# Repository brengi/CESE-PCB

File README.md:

# DCI- Curso de Diseño de Circuitos Impresos de la Carrera de Especialización en Sistemas Embebidos #

El Curso de Diseño de Circuitos Impresos (DCI) es una asignatura optativa de la Carrera de Especialización en Sistemas Embebidos (CESE) de la Facultad de Ingeniería de la Universidad de Buenos Aires (FIUBA). Tiene una duración de dos meses, organizados en 8 clases semanales de 3 hs cada una. Para aprobar la asignatura los participantes deben realizar el diseño de un circuito impreso a elección durante el curso. En esta página quedan registradas  dichas prácticas.

Más info sobre el curso en las siguiente páginas: 
  * [Contenido y Bibliografía](https://sites.google.com/site/disenodecircuitosimpresoscese/home)
  * [Campus FIUBA](https://campus.fi.uba.ar/enrol/index.php?id=1450])

**ADVERTENCIA**: Estos diseños se realizan en tiempos muy cortos y no todos reciben una revisión funcional detallada. 
El curso enfoca el los procedimientos de diseño de Esquemático y de PCB y no en el diseño funcional de los  circuitos.
El uso de estos circuitos queda bajo la propia responsabilidad del usuario. 

   * [CURSO 2020 B](README_2020B.md#curso-2020-b)
      * [Sistema Monitoreo Alarma de Incendio](README_2020B.md#sistema-monitoreo-alarma-de-incendio)
      * [Réplica dc motor control](README_2020B.md#réplica-dc-motor-control)
      * [Titulador automático](README_2020B.md#titulador-automático)
      * [Board_NFC (Replica sin antena)](README_2020B.md#board_nfc-replica-sin-antena)
      * [Poncho TCP/IP](README_2020B.md#poncho-tcpip)
      * [Replica ESP01 (Mejorada)](README_2020B.md#replica-esp01-mejorada)
      * [Driver motor PAP y ADC](README_2020B.md#driver-motor-pap-y-adc)
      * [Helctec LoRa con cambios](README_2020B.md#helctec-lora-con-cambios)
      * [Réplica pro micro sparkfun (similar)](README_2020B.md#réplica-pro-micro-sparkfun-similar)
      * [Conversor de niveles lógicos](README_2020B.md#conversor-de-niveles-lógicos)
      * [Réplica Sparkfun VS1063](README_2020B.md#réplica-sparkfun-vs1063)
      * [Módulo de velocidad tacométrico](README_2020B.md#módulo-de-velocidad-tacométrico)
      * [Réplica Arduino nano 340g 2016](README_2020B.md#réplica-arduino-nano-340g-2016)
      * [Beacon basado en DWM1001 (Réplica simplificada)](README_2020B.md#beacon-basado-en-dwm1001-réplica-simplificada)
      * [Réplica Pinguino PIC](README_2020B.md#réplica-pinguino-pic)
      * [Réplica detección de obstáculos por infrarrojo](README_2020B.md#réplica-detección-de-obstáculos-por-infrarrojo)
      * [Replica Adafruit HUZZAH32 - ESP32 Feather](README_2020B.md#replica-adafruit-huzzah32---esp32-feather)
      * [Poncho interfaz   arreglo sensores  IR](README_2020B.md#poncho-interfaz--arreglo-sensores--ir)
      * [Programador de microcontroladores](README_2020B.md#programador-de-microcontroladores)

   * [CURSO 2020 A](README_2020A.md#curso-2020-a)
      * [Escáner Magnético de Soldaduras](README_2020A.md#escáner-magnético-de-soldaduras)
      * [Replica Acelerómetro adxl345](README_2020A.md#replica-acelerómetro-adxl345)
      * [Monitor de medidores de energía eléctrica](README_2020A.md#monitor-de-medidores-de-energía-eléctrica)
      * [Réplica  modificada Heltec Wifi LoRA V2](README_2020A.md#réplica--modificada-heltec-wifi-lora-v2)
      * [Réplica Teensy 3.2](README_2020A.md#réplica-teensy-32)
      * [Poncho fotovoltaico](README_2020A.md#poncho-fotovoltaico)
      * [Módem Energy meter](README_2020A.md#módem-energy-meter)
      * [Poncho EDU-CIAA Drivers](README_2020A.md#poncho-edu-ciaa-drivers)

   * [CURSO 6  - 2019](README_2019.md#curso-6----2019)
      * [Punku, control de accesos](README_2019.md#punku-control-de-accesos)
      * [Cargador de batería con protección](README_2019.md#cargador-de-batería-con-protección)
      * [Replica EasyDriver v4.5](README_2019.md#replica-easydriver-v45)
      * [Poncho PLC CIAA 7](README_2019.md#poncho-plc-ciaa-7)
      * [Placa adaptadora de señales de radar](README_2019.md#placa-adaptadora-de-señales-de-radar)
      * [Driver I2C de leds RGB](README_2019.md#driver-i2c-de-leds-rgb)
      * [Encoder &amp; Driver PaP](README_2019.md#encoder--driver-pap)
      * [Dip Coater](README_2019.md#dip-coater)
      * [Driver motor CC](README_2019.md#driver-motor-cc)
      * [Controlador de motor con sensor](README_2019.md#controlador-de-motor-con-sensor)
      * [Placa Bridge Ethernet](README_2019.md#placa-bridge-ethernet)
      * [Fuente Step Up DC-DC ajustable 5v-35v](README_2019.md#fuente-step-up-dc-dc-ajustable-5v-35v)
   * [CURSO 5  - 2019](README_2019.md#curso-5----2019)
      * [Controlador de solenoides realimentado](README_2019.md#controlador-de-solenoides-realimentado)
      * [Módulo ESP8266 - nodeMCU](README_2019.md#módulo-esp8266---nodemcu)
      * [Amplificador biológico educativo](README_2019.md#amplificador-biológico-educativo)
      * [RS485 Port KP995](README_2019.md#rs485-port-kp995)
      * [Sistema de Monitoreo de Material Rodante](README_2019.md#sistema-de-monitoreo-de-material-rodante)
      * [Replica mejorada ESP32 Thing](README_2019.md#replica-mejorada-esp32-thing)
      * [Kit desarrollo para microcontrolador pic16f1939](README_2019.md#kit-desarrollo-para-microcontrolador-pic16f1939)
      * [Placa de desarrollo basado en una FPGA Libre](README_2019.md#placa-de-desarrollo-basado-en-una-fpga-libre)
      * [Poncho adaptador Arduino Mega2560](README_2019.md#poncho-adaptador-arduino-mega2560)
      * [Custom Raspberry Compute Module IO Board](README_2019.md#custom-raspberry-compute-module-io-board)
      * [Réplica TTGO-LORA32-V2.0](README_2019.md#réplica-ttgo-lora32-v20)

   * [CURSO 4  - 2018](README_2018.md#curso-4----2018)
      * [Driver motor pap](README_2018.md#driver-motor-pap)
      * [CIAA-UNO](README_2018.md#ciaa-uno)
      * [Poncho multimedia](README_2018.md#poncho-multimedia)
      * [Puente H doble de 20A](README_2018.md#puente-h-doble-de-20a)
      * [Poncho Alarma](README_2018.md#poncho-alarma)
      * [Réplica del modulo 8 reles de arduino](README_2018.md#réplica-del-modulo-8-reles-de-arduino)
      * [Réplica Acelerometro-mma7361](README_2018.md#réplica-acelerometro-mma7361)
      * [Nodo SisCoCaf](README_2018.md#nodo-siscocaf)
      * [VOIP Shield para Nucleo F767](README_2018.md#voip-shield-para-nucleo-f767)
      * [Poncho CAN](README_2018.md#poncho-can)
      * [Papilio DUO](README_2018.md#papilio-duo)
      * [Detector de sonido arduino](README_2018.md#detector-de-sonido-arduino)
      * [Extension de tarjeta HCAL](README_2018.md#extension-de-tarjeta-hcal)
      * [Contador de pasajeros](README_2018.md#contador-de-pasajeros)
      * [Prototipo Equipo AVL](README_2018.md#prototipo-equipo-avl)
      * [Electrodo Activo para Electromiografía](README_2018.md#electrodo-activo-para-electromiografía)
      * [Replica Placa Madre WEMB01](README_2018.md#replica-placa-madre-wemb01)
      * [Sistema de intercambio de mensajes de voz](README_2018.md#sistema-de-intercambio-de-mensajes-de-voz)
      * [VOP24](README_2018.md#vop24)
      * [PCB para alarma IoT](README_2018.md#pcb-para-alarma-iot)
      * [Modulo TPMS sensor](README_2018.md#modulo-tpms-sensor)
      * [Poncho Procesador de Audio](README_2018.md#poncho-procesador-de-audio)
      * [wifi ESP-01 con relés optoacoplados](README_2018.md#wifi-esp-01-con-relés-optoacoplados)

   * [CURSO 3  - 2017](README_2017.md#curso-3----2017)
      * [Poncho  MIDI](README_2017.md#poncho--midi)
      * [Poncho  Poncho WIFI BLUETOOTH ESP-WROOM-32](README_2017.md#poncho--poncho-wifi-bluetooth-esp-wroom-32)
      * [Poncho  Expansor de Puertos](README_2017.md#poncho--expansor-de-puertos)
      * [Poncho Control de temperatura](README_2017.md#poncho-control-de-temperatura)
      * [Poncho Joystick](README_2017.md#poncho-joystick)
      * [Poncho Medición de pH](README_2017.md#poncho-medición-de-ph)
      * [Poncho  RF](README_2017.md#poncho--rf)
      * [PicoPoncho Lora](README_2017.md#picoponcho-lora)
      * [Poncho Educativo Modelo 2](README_2017.md#poncho-educativo-modelo-2)
      * [Poncho USB-XBEE](README_2017.md#poncho-usb-xbee)
      * [PicoPoncho Bluetooth HC05](README_2017.md#picoponcho-bluetooth-hc05)
      * [Poncho  LCD y Botones](README_2017.md#poncho--lcd-y-botones)

   * [CURSO 2  - 2016](README_2016.md#curso-2----2016)
      * [PicoPoncho WiFi](README_2016.md#picoponcho-wifi)
      * [Poncho  Educativo](README_2016.md#poncho--educativo)
      * [Poncho IoT](README_2016.md#poncho-iot)
      * [Poncho  SAEv2](README_2016.md#poncho--saev2)
      * [Poncho  Puente H por i2C](README_2016.md#poncho--puente-h-por-i2c)
      * [Poncho Oxímetro](README_2016.md#poncho-oxímetro)
      * [Placa Educativa de la materia Electrónica Gral.](README_2016.md#placa-educativa-de-la-materia-electrónica-gral)
      * [Placa de desarrollo para LPC1114](README_2016.md#placa-de-desarrollo-para-lpc1114)
      * [Placa Control Vino](README_2016.md#placa-control-vino)
      * [PMOD Medidor de impedancia para FPGA](README_2016.md#pmod-medidor-de-impedancia-para-fpga)
      * [Poncho EDU-CIAA-NXP RF 2.4GHz Antena PCB](README_2016.md#poncho-edu-ciaa-nxp-rf-24ghz-antena-pcb)
      * [Poncho CNC](README_2016.md#poncho-cnc)
   * [CURSO 1  - 2016](README_2016.md#curso-1----2016)
      * [Poncho Celda de Carga](README_2016.md#poncho-celda-de-carga)
      * [Poncho Osciloscopio](README_2016.md#poncho-osciloscopio)
      * [Poncho Simon](README_2016.md#poncho-simon)
      * [Poncho Audio](README_2016.md#poncho-audio)
      * [Poncho Detector de Caídas](README_2016.md#poncho-detector-de-caídas)
      * [Poncho ECG](README_2016.md#poncho-ecg)
      * [Poncho L298](README_2016.md#poncho-l298)
      * [Poncho Misión SAE](README_2016.md#poncho-misión-sae)
      * [AislacionUSB](README_2016.md#aislacionusb)
      * [Proyecto MICR](README_2016.md#proyecto-micr)
      * [Proyecto Modular Drummer](README_2016.md#proyecto-modular-drummer)

Created by [gh-md-toc](https://github.com/ekalinin/github-markdown-toc)

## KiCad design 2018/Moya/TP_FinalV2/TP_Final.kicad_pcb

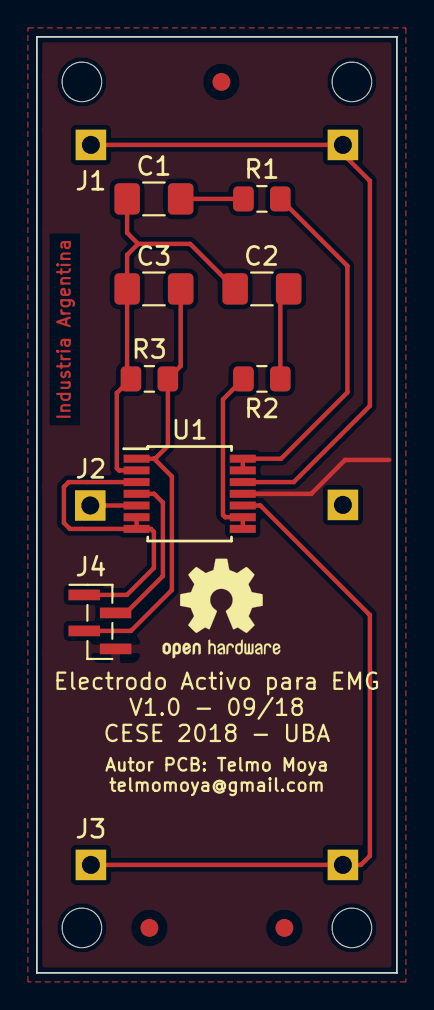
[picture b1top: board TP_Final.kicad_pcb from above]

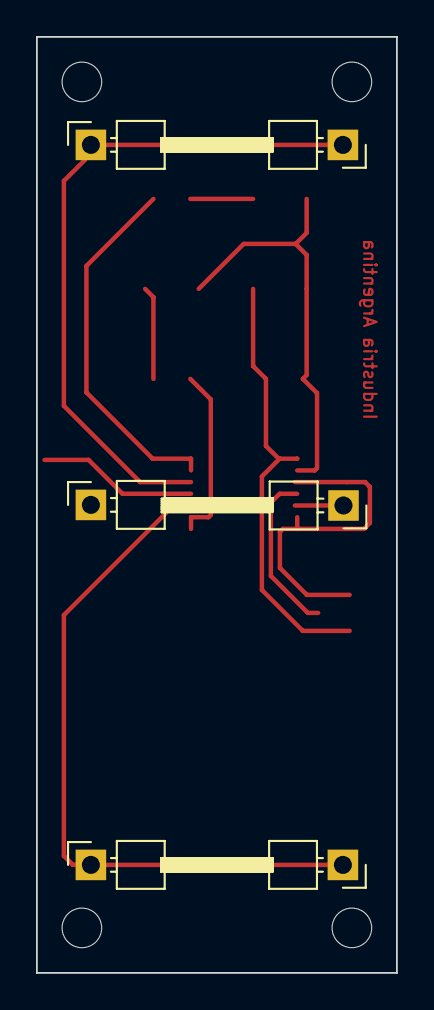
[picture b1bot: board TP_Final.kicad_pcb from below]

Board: 2 copper layers, 20.0 x 52.0 mm, 21 parts (6 on the bottom side), 12 nets.

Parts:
C1, C2: 10uF; C_1206_3216Metric_Pad1.42x1.75mm_HandSolder
C3: 32nF; C_1206_3216Metric_Pad1.42x1.75mm_HandSolder
F1, F2, F3: Fiducial; Fiducial_1mm_Dia_2mm_Outer
J1, J2, J3, J11, J22, J33: Conn_01x01_Male; PinHeader_1x01_P2.54mm_Horizontal
J4: Conn_01x04_Male; PinHeader_1x04_P1.00mm_Vertical_SMD_Pin1Left
MH1, MH2, MH3, MH4: MountingHole; MountingHole_2.2mm_M2
R1, R2: 1K; R_0805_2012Metric_Pad1.15x1.40mm_HandSolder
R3: 10K; R_0805_2012Metric_Pad1.15x1.40mm_HandSolder
U1: OPA4243; TSSOP-14_4.4x5mm_P0.65mm

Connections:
/Va: J1.1, J11.1, U1.12
/Vb: J2.1, U1.5
/Vc: J3.1, J33.1, U1.10
/Vo+: J4.1, U1.3, U1.6, U1.7
/Vo-: C3.2, J4.3, R3.2, U1.1
GND: J4.4, U1.11
unnamed: C1.1, C2.2, C3.1, R3.1, U1.2
unnamed: C1.2, R1.1
unnamed: C2.1, R2.1
unnamed: R1.2, U1.13, U1.14
unnamed: R2.2, U1.8, U1.9
VCC: J4.2, U1.4

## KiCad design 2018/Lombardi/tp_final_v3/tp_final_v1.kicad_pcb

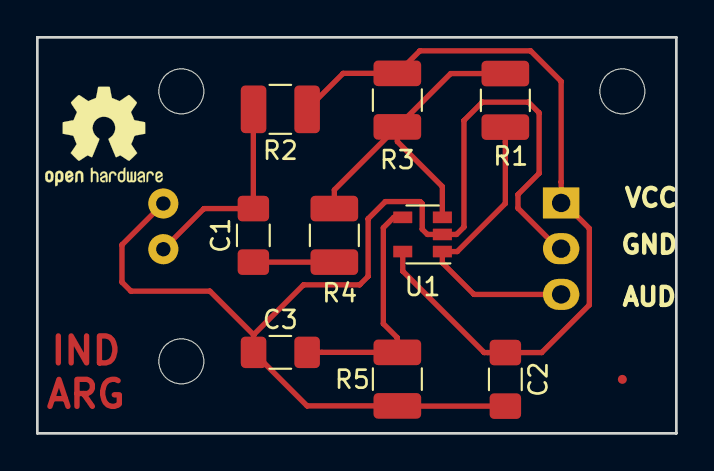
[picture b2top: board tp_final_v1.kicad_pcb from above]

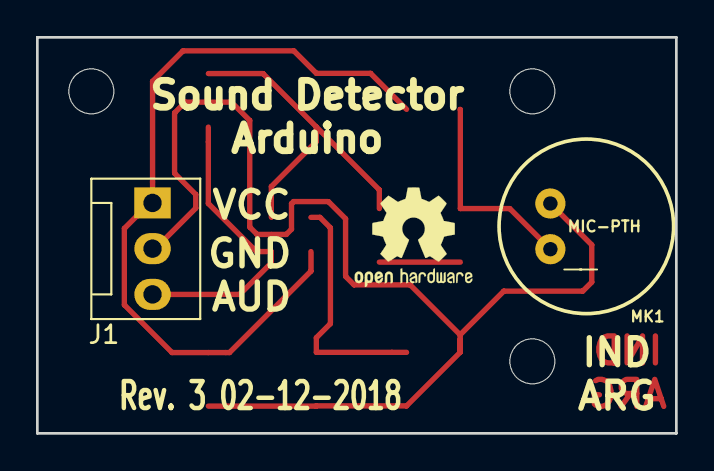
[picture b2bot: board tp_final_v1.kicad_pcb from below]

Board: 2 copper layers, 35.5 x 22.0 mm, 15 parts (2 on the bottom side), 7 nets.

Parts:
C1, C3: 4.7uF; C_1206_3216Metric_Pad1.42x1.75mm_HandSolder
C2: 0.1uF; C_1206_3216Metric_Pad1.42x1.75mm_HandSolder
J1: Conn_01x03; FanPinHeader_1x03_P2.54mm_Vertical
MH1, MH2, MH3: MountingHole; MountingHole_2.5mm
MH4: Fiducial; Fiducial_0.5mm_Dia_1mm_Outer
MK1: MIC-PTH; MICROPHONE-PTH-9.7MM
R1: 820k; R_1210_3225Metric_Pad1.42x2.65mm_HandSolder
R2: 2.2k; R_1210_3225Metric_Pad1.42x2.65mm_HandSolder
R3, R4, R5: 10k; R_1210_3225Metric_Pad1.42x2.65mm_HandSolder
U1: OPA340NA; SOT-23-5

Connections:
GND: C2.2, C3.1, J1.2, MK1.OUT, R5.2, U1.2
unnamed: C1.1, R4.2
unnamed: C1.2, MK1.GND, R2.2
unnamed: C3.2, R5.1, U1.4
unnamed: J1.3, R1.1, U1.1
unnamed: R1.2, R3.2, R4.1, U1.3
VCC: C2.1, J1.1, R2.1, R3.1, U1.5

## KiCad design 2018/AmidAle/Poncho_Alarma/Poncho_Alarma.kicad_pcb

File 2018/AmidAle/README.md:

# CESE18_PCB_Amid_Ale
Trabajo final de la asignatura Diseño de PCB de la CESE

** Principales Características:**

1. Salidas a Relay (2)
2. Entradas Optoacopladas (4)
4. (RS232) ESP8266 (1)
5. Display 16x2 (1)

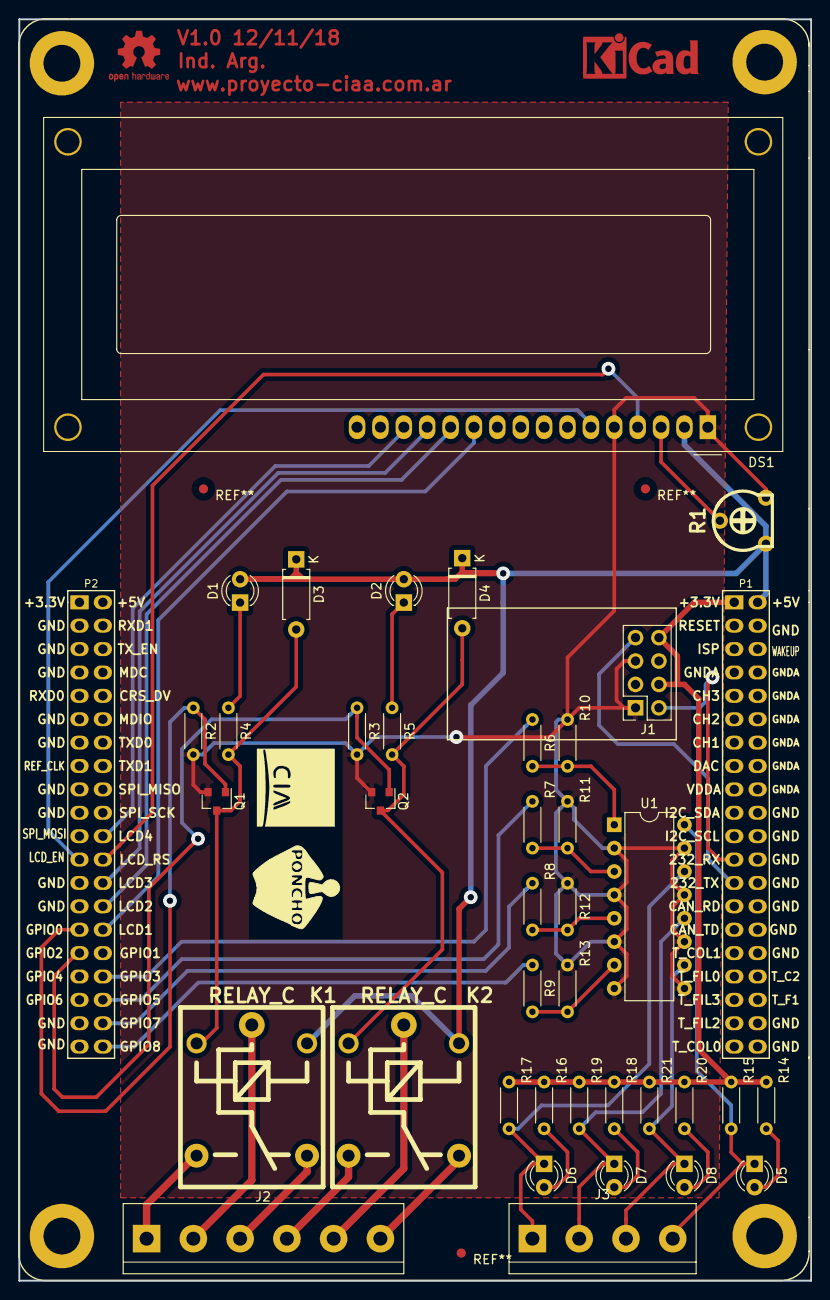
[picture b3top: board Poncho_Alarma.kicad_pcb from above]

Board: 2 copper layers, 86.0 x 137.0 mm, 40 parts (0 on the bottom side), 40 nets.

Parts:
D1, D2, D5, D6, D7, D8: LED_Rojo; LED_D3.0mm
D3, D4: LL4148; D_A-405_P7.62mm_Horizontal
DS1: LCD16X2; WC1602A
G102: LOGO_CIAA; LOGO-CIAA
J1: ESP8266; ESP-01
J2: Salidas; TerminalBlock_bornier-6_P5.08mm
J3: Entradas; TerminalBlock_bornier-4_P5.08mm
K1, K2: RELAY_C; Relay_C
Q1, Q2: 2N7002; SOT-23
R1: 10K; TRIMER_V
R2, R3: 100k; R_Axial_DIN0204_L3.6mm_D1.6mm_P5.08mm_Horizontal
R4, R5: 330; R_Axial_DIN0204_L3.6mm_D1.6mm_P5.08mm_Horizontal
R6, R7, R8, R9: R_Small3.3K; R_Axial_DIN0204_L3.6mm_D1.6mm_P5.08mm_Horizontal
R10, R11, R12, R13: 4.7K; R_Axial_DIN0204_L3.6mm_D1.6mm_P5.08mm_Horizontal
R14, R16, R18, R20: 2.2K; R_Axial_DIN0204_L3.6mm_D1.6mm_P5.08mm_Horizontal
R15, R17, R19, R21: 100K; R_Axial_DIN0204_L3.6mm_D1.6mm_P5.08mm_Horizontal
U1: TLP627-4; DIP-16_W7.62mm
XA1: Conn_Poncho2P_2x_20x2; poncho_grande

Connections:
+3V3: J1.4, J1.8, R14.1, R15.1, R16.1, R17.1, R18.1, R19.1, R20.1, R21.1, XA1.1
+5V: D1.2, D2.2, D3.1, D4.1, DS1.2, K1.5, K2.5, R1.1, XA1.2
/Entradas/In_1: R7.1, XA1.76
/Entradas/In_2: R8.1, XA1.78
/Entradas/In_3: R9.1, XA1.80
/Entradas/In_4: R6.1, XA1.74
/Salidas/K1_C: J2.2, K1.1
/Salidas/K1_NA: J2.1, K1.3
/Salidas/K1_NC: J2.3, K1.4
/Salidas/K2_C: J2.5, K2.1
/Salidas/K2_NA: J2.4, K2.3
/Salidas/K2_NC: J2.6, K2.4
/Salidas/Out_1: Q1.1, R2.1, XA1.69
/Salidas/Out_2: Q2.1, R3.1, XA1.71
GND: DS1.1, DS1.5, J1.1, J1.5, Q1.2, Q2.2, R1.3, R2.2, R3.2, R10.1, R11.1, R12.1, R13.1, U1.2, U1.4, U1.6, U1.8, U1.9, U1.11, U1.13, U1.15
unnamed: D1.1, R4.1
unnamed: D2.1, R5.1
unnamed: D3.2, K1.2, Q1.3, R4.2
unnamed: D4.2, K2.2, Q2.3, R5.2
unnamed: D5.1, J3.4, R15.2, U1.16
unnamed: D5.2, R14.2
unnamed: D6.1, J3.1, R17.2, U1.14
unnamed: D6.2, R16.2
unnamed: D7.1, J3.2, R19.2, U1.12
unnamed: D7.2, R18.2
unnamed: D8.1, J3.3, R21.2, U1.10
unnamed: D8.2, R20.2
unnamed: DS1.3, R1.2
unnamed: DS1.4, XA1.64
unnamed: DS1.6, XA1.63
unnamed: DS1.11, XA1.70
unnamed: DS1.12, XA1.68
unnamed: DS1.13, XA1.66
unnamed: DS1.14, XA1.62
unnamed: J1.2, XA1.23
unnamed: J1.7, XA1.25
unnamed: R6.2, R10.2, U1.1
unnamed: R7.2, R11.2, U1.3
unnamed: R8.2, R12.2, U1.5
unnamed: R9.2, R13.2, U1.7

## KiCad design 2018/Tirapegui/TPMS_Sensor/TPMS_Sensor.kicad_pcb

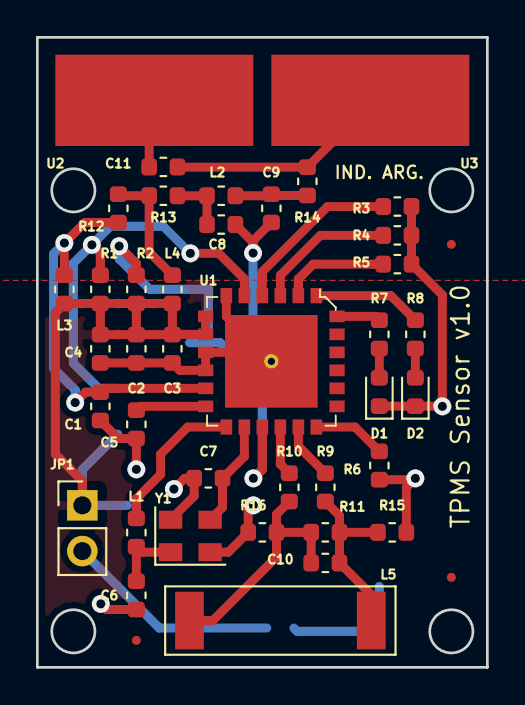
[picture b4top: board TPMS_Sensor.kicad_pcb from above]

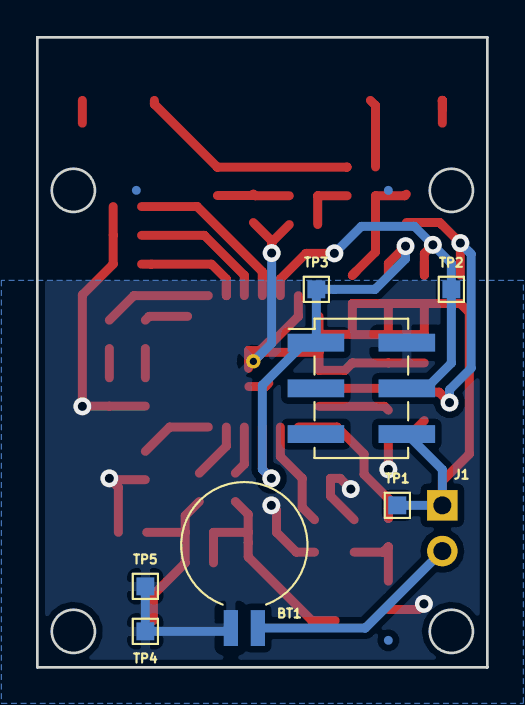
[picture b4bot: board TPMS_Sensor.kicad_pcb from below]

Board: 2 copper layers, 25.0 x 35.0 mm, 52 parts (10 on the bottom side), 27 nets.

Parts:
BT1: Battery_Cell; BatteryHolder_Seiko_MS621F
C1: 1.5pF; C_0603_1608Metric
C2: 0.1uF; C_0603_1608Metric
C3: 100pF; C_0603_1608Metric
C4, C8, C11: DNP; C_0603_1608Metric
C5: 0.47uF; C_0603_1608Metric
C6, C7: 10pF; C_0603_1608Metric
C9: 1pF; C_0603_1608Metric
C10: 220pF; C_0603_1608Metric
D1: LED_A; LED_0603_1608Metric
D2: LED_B; LED_0603_1608Metric
F1, F2, F3, F4, F5, F6: Fiducial; Fiducial_0.5mm_Dia_1mm_Outer
J1: Conn_02x03_Odd_Even; PinHeader_2x03_P2.54mm_Vertical_SMD
JP1: Jumper; PinHeader_1x02_P2.54mm_Vertical
L1: 10nH; L_0603_1608Metric
L2: 100nH; L_0603_1608Metric
L3: DNP; L_0603_1608Metric
L4: 39nH; L_0603_1608Metric
L5: 7.2mH; LFCoil_B82450A7204A000
R1, R2: 4k7; R_0603_1608Metric
R3, R4, R5, R6, R7, R8, R15, R16: DNP; R_0603_1608Metric
R9, R10, R12, R13, R14: 0; R_0603_1608Metric
R11: 10k; R_0603_1608Metric
TP1, TP2, TP3, TP4, TP5: TestPoint; TestPoint_Pad_1.0x1.0mm
U1: FXTH87xxxx; QFN-24_7x7mm
U2: PAD1; RF_Antenna_PAD
U3: PAD2; RF_Antenna_PAD
Y1: Xtal; Crystal_SMD_EuroQuartz_MT-4Pin_3.2x2.5mm

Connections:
+BATT: C2.1, C3.1, C4.1, J1.6, JP1.1, L3.2, L4.2, R1.2, R2.1, TP1.1, U1.7, U1.8
GND: BT1.2, C1.2, C2.2, C3.2, C4.2, C5.2, C6.2, C7.2, C8.2, C9.2, D1.1, D2.1, J1.2, R3.2, R4.2, R5.2, R6.2, R15.1, R16.1, TP4.1, TP5.1, U1.6, U1.9, U1.10, U1.25, Y1.2, Y1.4
unnamed: BT1.1, JP1.2
unnamed: C1.1, L3.1, R12.1, U1.11
unnamed: C5.1, U1.12
unnamed: C6.1, L1.2, Y1.1
unnamed: C7.1, U1.14, Y1.3
unnamed: C8.1, L2.1, R13.2
unnamed: C9.1, L2.2, R14.2
unnamed: C10.1, L5.2, R10.1, R11.1, R16.2
unnamed: C10.2, L5.1, R9.1, R11.2, R15.2
unnamed: C11.1, U2.1
unnamed: C11.2, R14.1, U3.1
unnamed: D1.2, R7.2
unnamed: D2.2, R8.2
unnamed: J1.1, R2.2, TP3.1, U1.15
unnamed: J1.4, R1.1, TP2.1, U1.5
unnamed: L1.1, U1.13
unnamed: L4.1, R12.2, R13.1
unnamed: R3.1, U1.4
unnamed: R4.1, U1.3
unnamed: R5.1, U1.2
unnamed: R6.1, U1.18
unnamed: R7.1, U1.24
unnamed: R8.1, U1.1
unnamed: R9.2, U1.17
unnamed: R10.2, U1.16

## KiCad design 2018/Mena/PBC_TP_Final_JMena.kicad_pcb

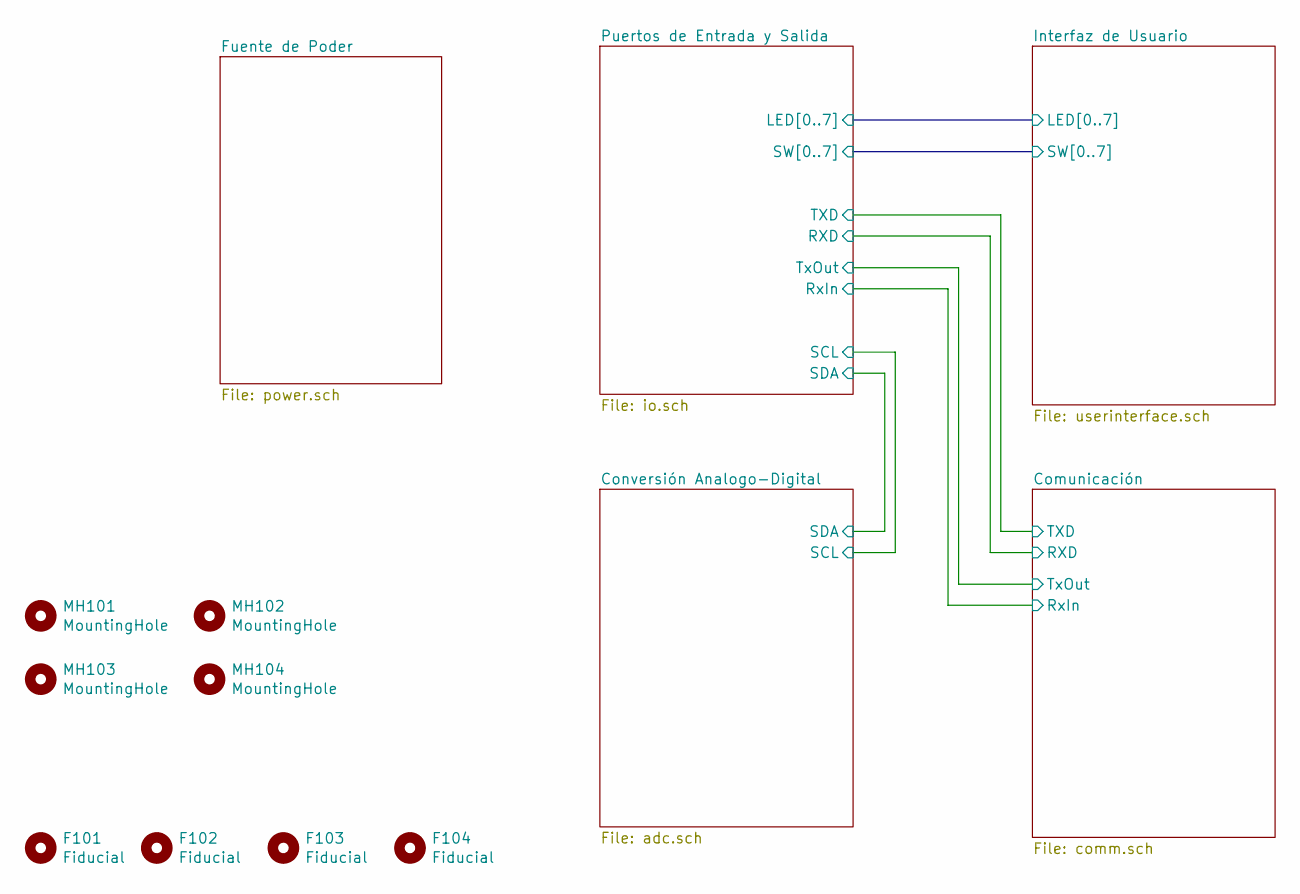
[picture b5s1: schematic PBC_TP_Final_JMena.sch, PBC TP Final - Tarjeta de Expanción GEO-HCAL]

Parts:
F101, F102, F103, F104: Fiducial; Fiducial_0.75mm_Dia_1.5mm_Outer
MH101, MH102, MH103, MH104: MountingHole; MountingHole_2.5mm

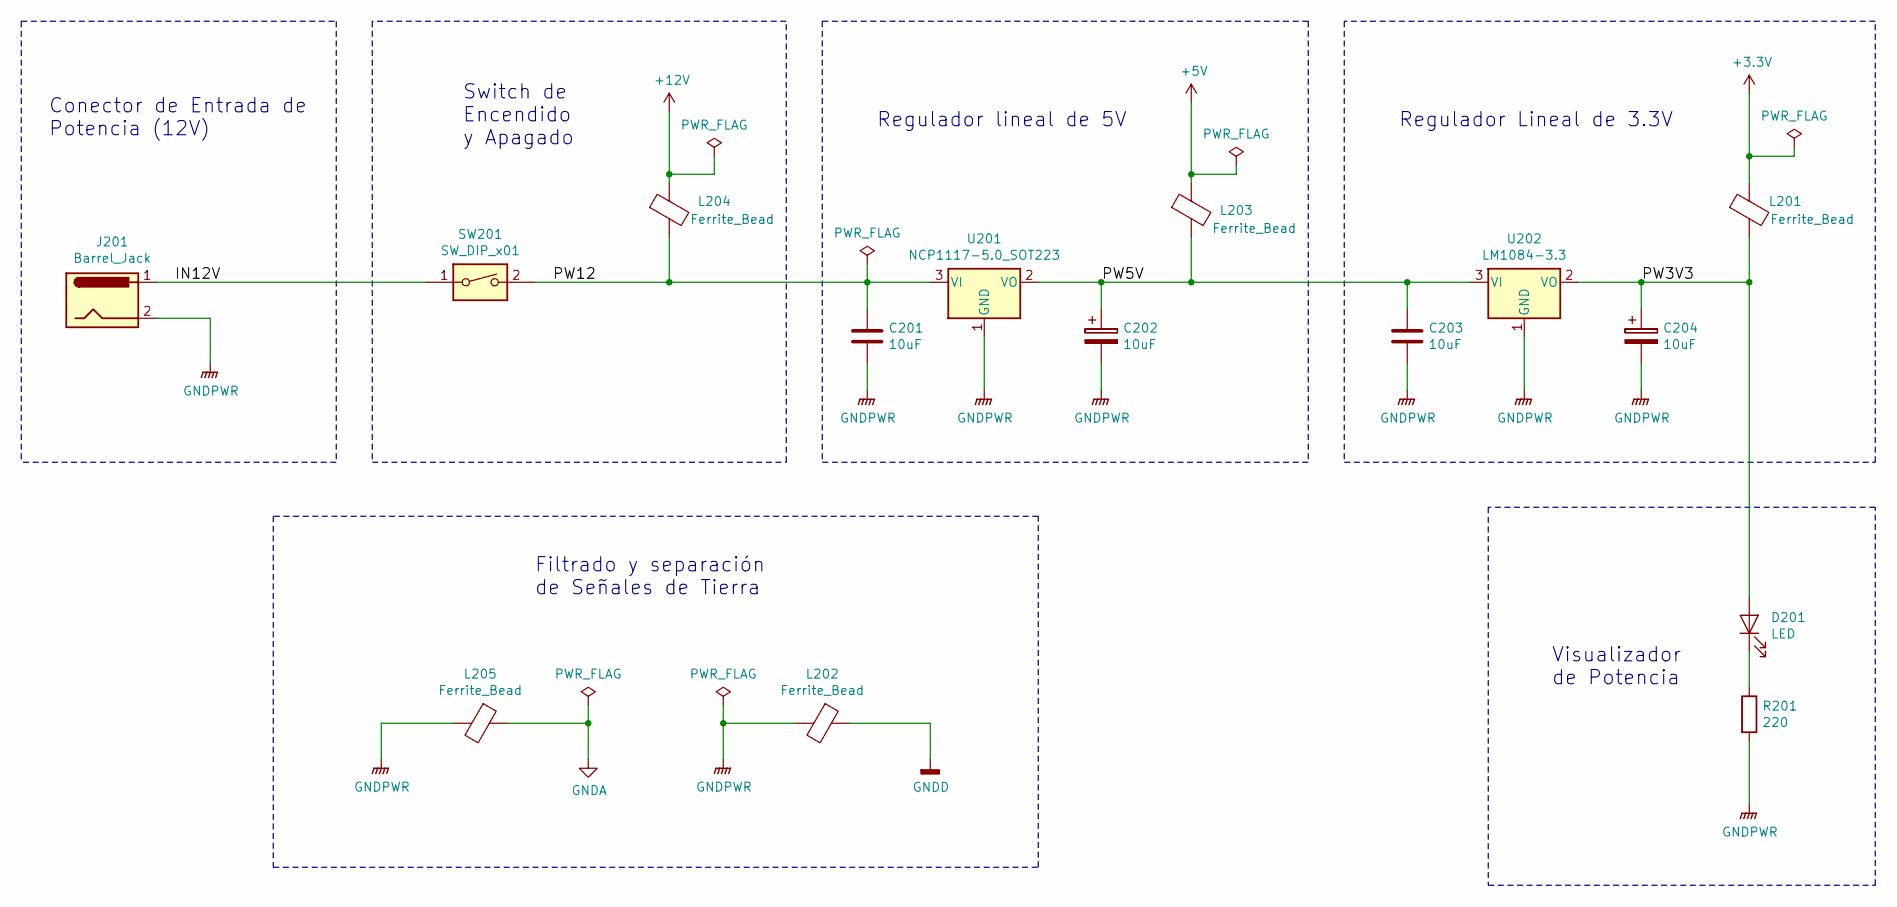
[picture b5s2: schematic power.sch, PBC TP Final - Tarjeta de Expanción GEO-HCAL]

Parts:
C201, C202, C203, C204: 10uF; C_1206_3216Metric_Pad1.42x1.75mm_HandSolder
D201: LED; LED_0805_2012Metric_Pad1.15x1.40mm_HandSolder
J201: Barrel_Jack; BarrelJack_CUI_PJ-063AH_Horizontal
L201, L202, L203, L204, L205: Ferrite_Bead; L_1206_3216Metric_Pad1.42x1.75mm_HandSolder
R201: 220; R_0805_2012Metric_Pad1.15x1.40mm_HandSolder
SW201: SW_DIP_x01; SW_SPST_EVQPE1
U201: NCP1117-5.0_SOT223; SOT-223-3_TabPin2
U202: LM1084-3.3; TO-263-3_TabPin2

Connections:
+5V: L203.1; also elsewhere on the board
+12V: L204.1; also elsewhere on the board
/Fuente de Poder/IN12V: J201.1, SW201.1
/Fuente de Poder/PW3V3: C204.1, D201.2 (A), L201.2, U202.2 (VO)
/Fuente de Poder/PW5V: C202.1, C203.1, L203.2, U201.2 (VO), U202.3 (VI)
/Fuente de Poder/PW12: C201.1, L204.2, SW201.2, U201.3 (VI)
GNDA: L205.1; also elsewhere on the board
GNDD: L202.1; also elsewhere on the board
GNDPWR: C201.2, C202.2, C203.2, C204.2, J201.2, L202.2, L205.2, R201.2, U201.1 (GND), U202.1 (GND)
unnamed: D201.1 (K), R201.1

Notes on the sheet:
Conector de Entrada de Potencia (12V)
Regulador lineal de 5V
Regulador Lineal de 3.3V
Visualizador de Potencia
Filtrado y separación de Señales de Tierra
Switch de Encendido y Apagado

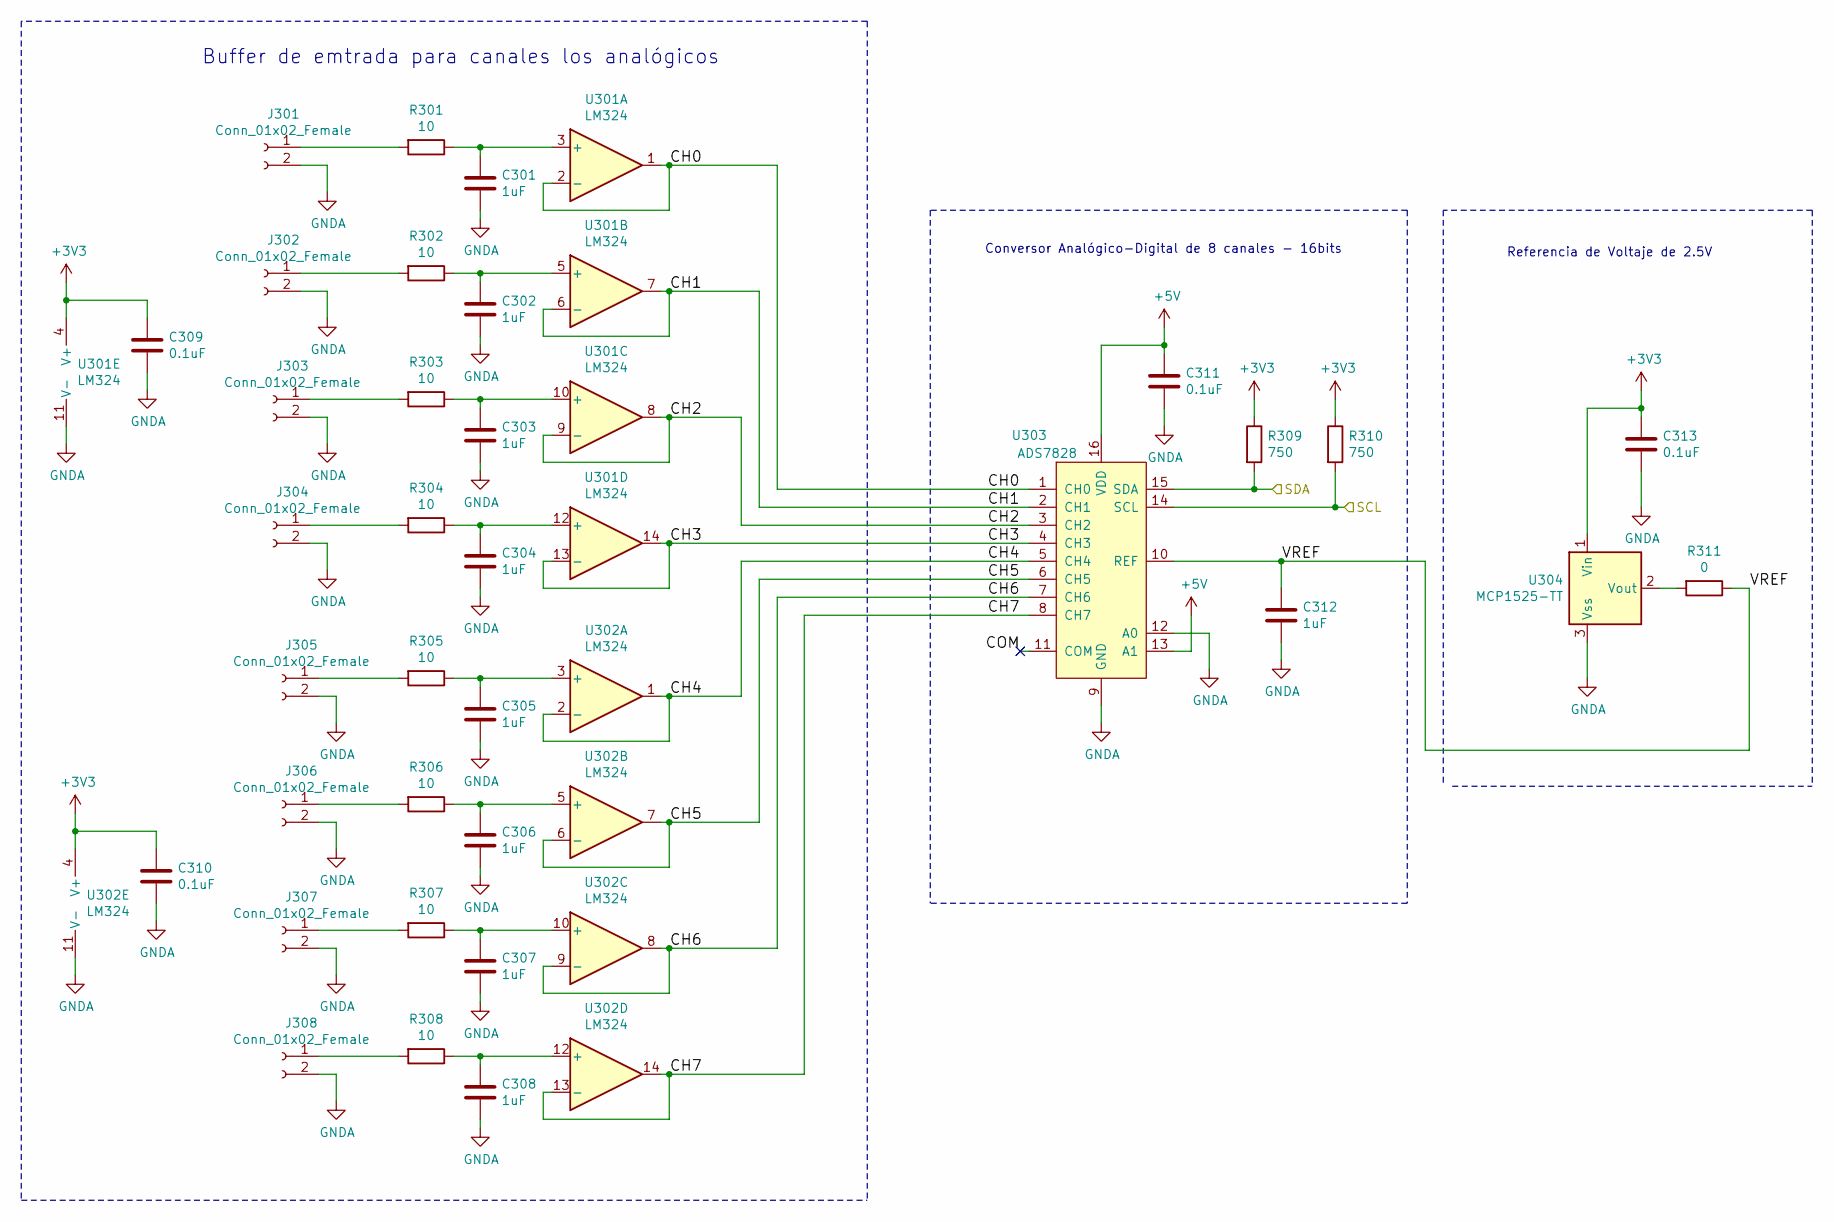
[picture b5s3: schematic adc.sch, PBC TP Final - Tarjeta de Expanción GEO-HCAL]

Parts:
C301, C302, C303, C304, C305, C306, C307, C308, C312: 1uF; C_0805_2012Metric_Pad1.15x1.40mm_HandSolder
C309, C310, C311, C313: 0.1uF; C_0805_2012Metric_Pad1.15x1.40mm_HandSolder
J301, J302, J303, J304, J305, J306, J307, J308: Conn_01x02_Female; PinHeader_1x02_P1.27mm_Vertical
R301, R302, R303, R304, R305, R306, R307, R308: 10; R_0805_2012Metric_Pad1.15x1.40mm_HandSolder
R309, R310: 750; R_0805_2012Metric_Pad1.15x1.40mm_HandSolder
R311: 0; R_0805_2012Metric_Pad1.15x1.40mm_HandSolder
U301, U302: LM324; SOIC-14_3.9x8.7mm_P1.27mm
U303: ADS7828; TSSOP-16_4.4x5mm_P0.65mm
U304: MCP1525-TT; SOT-23

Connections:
+5V: C311.1, U303.13 (A1), U303.16 (VDD); also elsewhere on the board
/Conversión Analogo-Digital/CH0: U301.1, U301.2 (-), U303.1 (CH0)
/Conversión Analogo-Digital/CH1: U301.6 (-), U301.7, U303.2 (CH1)
/Conversión Analogo-Digital/CH2: U301.8, U301.9 (-), U303.3 (CH2)
/Conversión Analogo-Digital/CH3: U301.13 (-), U301.14, U303.4 (CH3)
/Conversión Analogo-Digital/CH4: U302.1, U302.2 (-), U303.5 (CH4)
/Conversión Analogo-Digital/CH5: U302.6 (-), U302.7, U303.6 (CH5)
/Conversión Analogo-Digital/CH6: U302.8, U302.9 (-), U303.7 (CH6)
/Conversión Analogo-Digital/CH7: U302.13 (-), U302.14, U303.8 (CH7)
/Conversión Analogo-Digital/COM: U303.11 (COM)
/Conversión Analogo-Digital/SCL: R310.2, U303.14 (SCL); also elsewhere on the board
/Conversión Analogo-Digital/SDA: R309.2, U303.15 (SDA); also elsewhere on the board
/Conversión Analogo-Digital/VREF: C312.1, R311.1, U303.10 (REF)
GNDA: C301.2, C302.2, C303.2, C304.2, C305.2, C306.2, C307.2, C308.2, C309.2, C310.2, C311.2, C312.2, C313.2, J301.2, J302.2, J303.2, J304.2, J305.2, J306.2, J307.2, J308.2, U301.11 (V-), U302.11 (V-), U303.9 (GND), U303.12 (A0), U304.3 (Vss); also elsewhere on the board
unnamed: C301.1, R301.1, U301.3 (+)
unnamed: C302.1, R302.1, U301.5 (+)
unnamed: C303.1, R303.1, U301.10 (+)
unnamed: C304.1, R304.1, U301.12 (+)
unnamed: C305.1, R305.1, U302.3 (+)
unnamed: C306.1, R306.1, U302.5 (+)
unnamed: C307.1, R307.1, U302.10 (+)
unnamed: C308.1, R308.1, U302.12 (+)
unnamed: J301.1, R301.2
unnamed: J302.1, R302.2
unnamed: J303.1, R303.2
unnamed: J304.1, R304.2
unnamed: J305.1, R305.2
unnamed: J306.1, R306.2
unnamed: J307.1, R307.2
unnamed: J308.1, R308.2
unnamed: R311.2, U304.2 (Vout)

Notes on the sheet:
Buffer de emtrada para canales los analógicos
Conversor Analógico-Digital de 8 canales - 16bits
Referencia de Voltaje de 2.5V

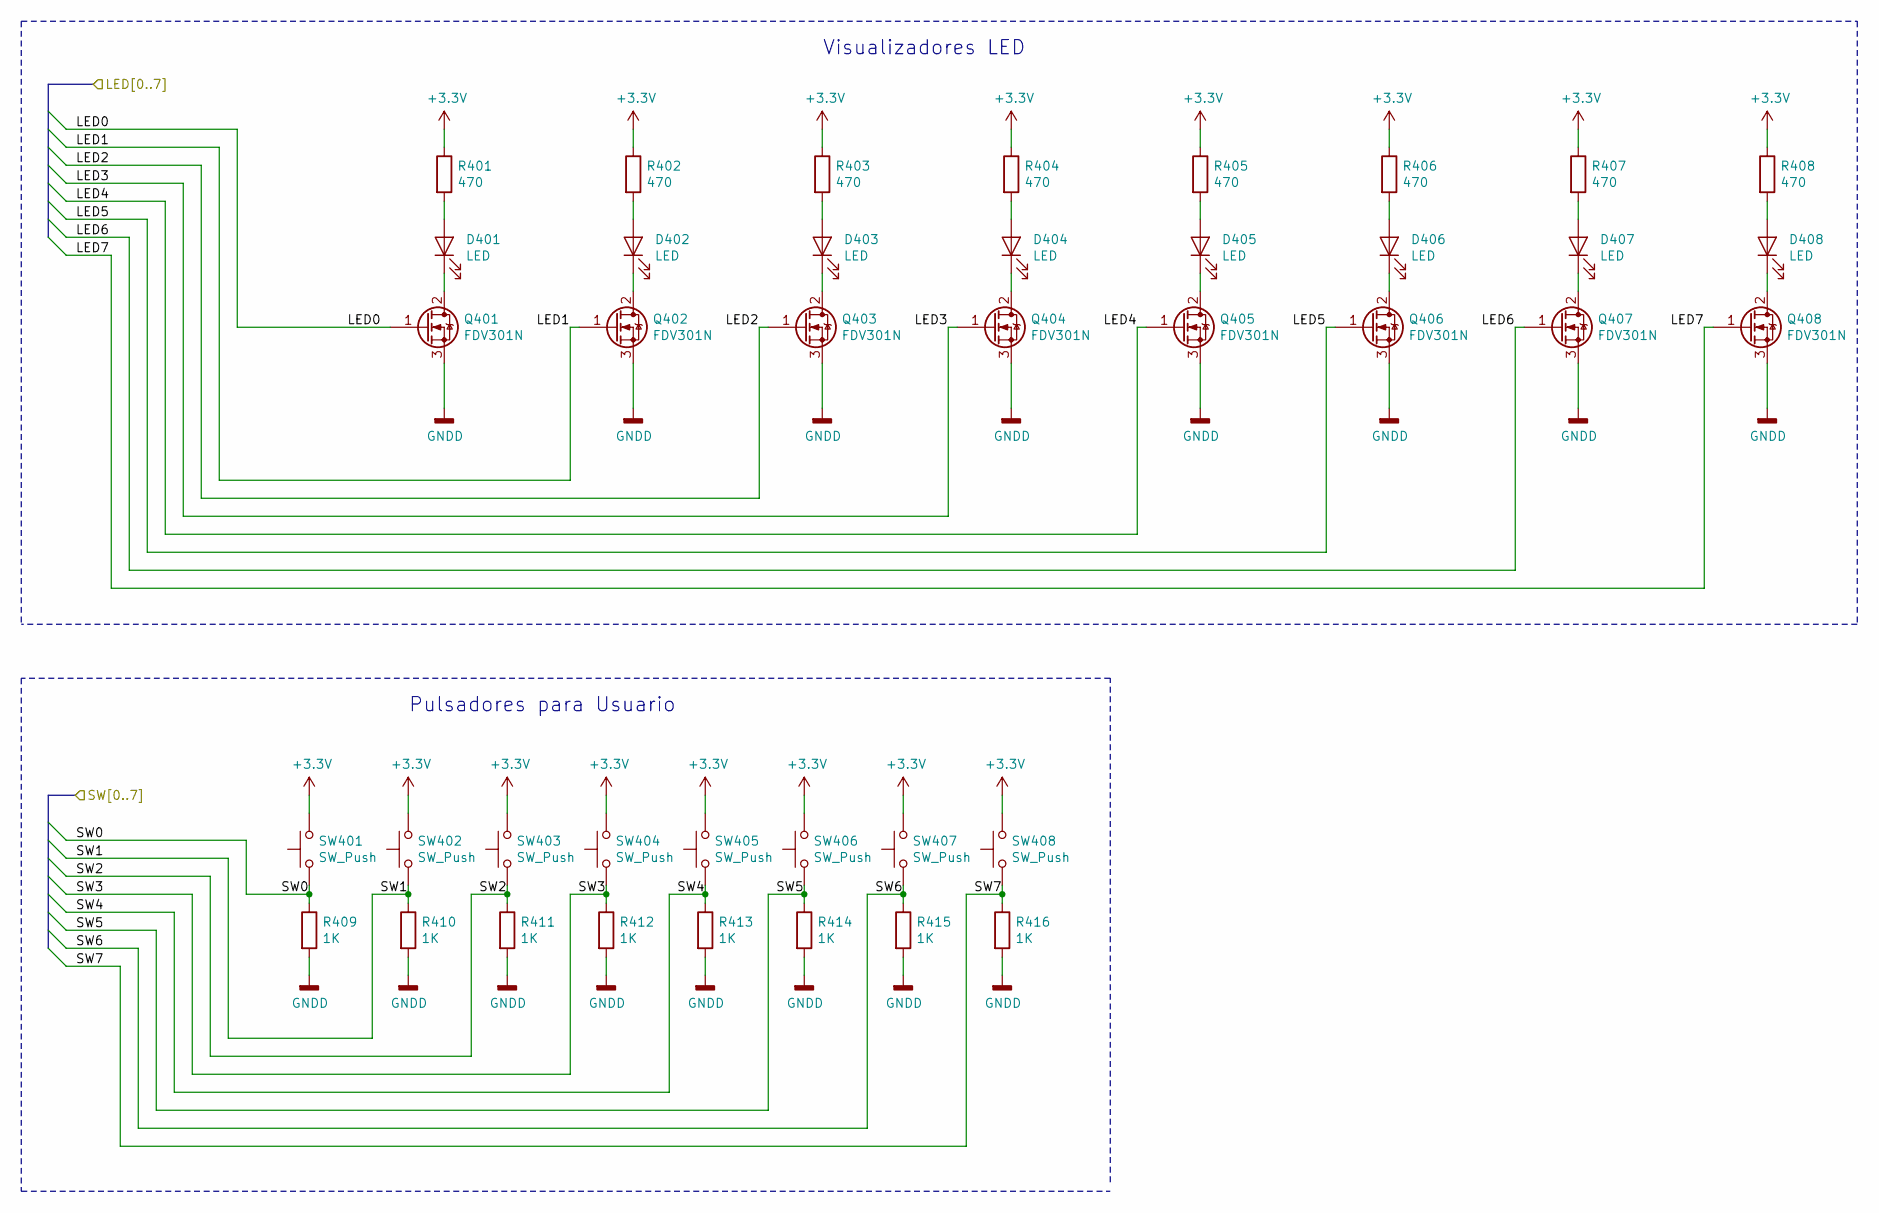
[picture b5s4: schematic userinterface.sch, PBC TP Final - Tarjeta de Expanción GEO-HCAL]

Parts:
D401, D402, D403, D404, D405, D406, D407, D408: LED; LED_0805_2012Metric_Pad1.15x1.40mm_HandSolder
Q401, Q402, Q403, Q404, Q405, Q406, Q407, Q408: FDV301N; SOT-23
R401, R402, R403, R404, R405, R406, R407, R408: 470; R_0805_2012Metric_Pad1.15x1.40mm_HandSolder
R409, R410, R411, R412, R413, R414, R415, R416: 1K; R_0805_2012Metric_Pad1.15x1.40mm_HandSolder
SW401, SW402, SW403, SW404, SW405, SW406, SW407, SW408: SW_Push; SW_SPST_B3U-1000P

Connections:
/Interfaz de Usuario/LED0: Q401.1 (G); also elsewhere on the board
/Interfaz de Usuario/LED1: Q402.1 (G); also elsewhere on the board
/Interfaz de Usuario/LED2: Q403.1 (G); also elsewhere on the board
/Interfaz de Usuario/LED3: Q404.1 (G); also elsewhere on the board
/Interfaz de Usuario/LED4: Q405.1 (G); also elsewhere on the board
/Interfaz de Usuario/LED5: Q406.1 (G); also elsewhere on the board
/Interfaz de Usuario/LED6: Q407.1 (G); also elsewhere on the board
/Interfaz de Usuario/LED7: Q408.1 (G); also elsewhere on the board
/Interfaz de Usuario/SW0: R409.1, SW401.1; also elsewhere on the board
/Interfaz de Usuario/SW1: R410.1, SW402.1; also elsewhere on the board
/Interfaz de Usuario/SW2: R411.1, SW403.1; also elsewhere on the board
/Interfaz de Usuario/SW3: R412.1, SW404.1; also elsewhere on the board
/Interfaz de Usuario/SW4: R413.1, SW405.1; also elsewhere on the board
/Interfaz de Usuario/SW5: R414.1, SW406.1; also elsewhere on the board
/Interfaz de Usuario/SW6: R415.1, SW407.1; also elsewhere on the board
/Interfaz de Usuario/SW7: R416.1, SW408.1; also elsewhere on the board
GNDD: Q401.3 (S), Q402.3 (S), Q403.3 (S), Q404.3 (S), Q405.3 (S), Q406.3 (S), Q407.3 (S), Q408.3 (S), R409.2, R410.2, R411.2, R412.2, R413.2, R414.2, R415.2, R416.2; also elsewhere on the board
unnamed: D401.1 (K), Q401.2 (D)
unnamed: D401.2 (A), R401.2
unnamed: D402.1 (K), Q402.2 (D)
unnamed: D402.2 (A), R402.2
unnamed: D403.1 (K), Q403.2 (D)
unnamed: D403.2 (A), R403.2
unnamed: D404.1 (K), Q404.2 (D)
unnamed: D404.2 (A), R404.2
unnamed: D405.1 (K), Q405.2 (D)
unnamed: D405.2 (A), R405.2
unnamed: D406.1 (K), Q406.2 (D)
unnamed: D406.2 (A), R406.2
unnamed: D407.1 (K), Q407.2 (D)
unnamed: D407.2 (A), R407.2
unnamed: D408.1 (K), Q408.2 (D)
unnamed: D408.2 (A), R408.2

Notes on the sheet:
Visualizadores LED
Pulsadores para Usuario

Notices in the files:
2018/Company/SisCoCaf/SisCoCaf.kicad_pcb:
Licencia Creative Commons
2018/Salamandri/RegulacionTensionEntrada.sch:
Licencia: Creative Commons - Attribution - ShareAlike 3.0
